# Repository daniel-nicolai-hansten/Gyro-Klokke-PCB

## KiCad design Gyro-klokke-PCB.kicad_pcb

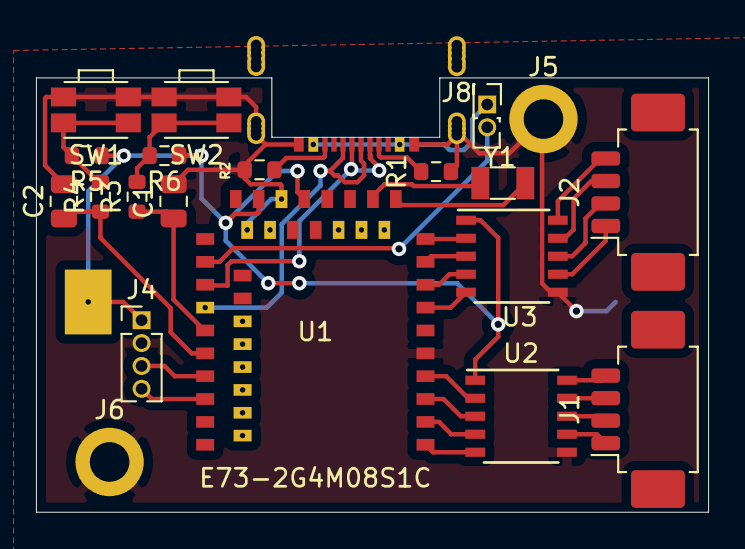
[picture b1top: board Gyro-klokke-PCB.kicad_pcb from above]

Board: 2 copper layers, 37.3 x 24.1 mm, 22 parts (1 on the bottom side), 32 nets.

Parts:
BT1: Battery_Cell; BatteryHolder_Keystone_1060_1x2032
C1, C2: 100nF; C_0805_2012Metric
J1, J2: Conn_01x04_Male; Molex_PicoBlade_53261-0471_1x04-1MP_P1.25mm_Horizontal
J4: Conn_01x04_Male; PinHeader_1x04_P1.27mm_Vertical
J5, J6: Conn_01x01_Female; MountingHole_2.2mm_M2_ISO14580_Pad
J7: USB_C_Receptacle_USB2.0; USB-C_C168688
J8: Conn_01x02_Female; PinHeader_2x01_P1.27mm_Vertical
R1, R2: 5.7K; R_0603_1608Metric
R3, R4, R5, R6: 10K; R_0603_1608Metric
SW1, SW2: SW_Push; SW_SPST_EVQP7A
U1: E73-2G4M08S1C-52840
U2, U3: LB1948MC; SSOP-10_3.9x4.9mm_P1.00mm
Y1: Crystal_Small; Crystal_SMD_3215-2Pin_3.2x1.5mm

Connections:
+3V3: BT1.1, J4.1, R5.1, R6.1, U1.19, U1.23, U2.1, U3.1
/D+: J7.A6, J7.B6, U1.31
/D-: J7.A7, J7.B7, U1.29
/VBUS: J7.A4, J8.1
GNDREF: BT1.2, C1.2, C2.2, J4.2, J5.1, J6.1, J7.A1, J7.S1, R1.1, R2.1, SW1.2, SW2.2, U1.5, U1.21, U1.24, U2.6, U3.6
unnamed: J1.1, U2.7
unnamed: J1.2, U2.8
unnamed: J1.3, U2.9
unnamed: J1.4, U2.10
unnamed: J2.1, U3.7
unnamed: J2.2, U3.8
unnamed: J2.3, U3.9
unnamed: J2.4, U3.10
unnamed: J7.A5, R1.2
unnamed: J7.B5, R2.2
unnamed: J8.2, U1.27
unnamed: R3.2, R6.2, SW2.1
unnamed: R4.2, R5.2, SW1.1
unnamed: U1.11, Y1.1
unnamed: U1.13, Y1.2
SWC: J4.4, U1.39
SWD: J4.3, U1.37
mot1-A1: U1.4, U2.2
mot1-A2: U1.3, U2.3
mot1-B1: U1.2, U2.4
mot1-B2: U1.1, U2.5
mot2-A1: U1.10, U3.2
mot2-A2: U1.9, U3.3
mot2-B1: U1.8, U3.4
mot2-B2: U1.7, U3.5
sw1: C2.1, R4.1, U1.35
sw2: C1.1, R3.1, U1.33

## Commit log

2020-12-03 Kretskort ferdig v1.0
2020-12-04 Kretskort ferdig v1.0, la til gnd på rtc cap
2020-12-06 rev1.0 RC1
2021-05-19 før nrf52
2021-05-20 endret stm32 til nrf
2023-02-04 Fikset ting
